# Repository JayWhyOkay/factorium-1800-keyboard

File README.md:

# Factorium Keyboard

Factorium is a keyboard in CP layout inspired by CFTKB's Discipline and Mysterium Keyboard

**Project is in hiatus indefinitely until further notice **

## Differences between Mysterium and Factorium
- Added numpad 
- Move arrow keys down and right
- Addition of F13
- Removal of two navigation buttons 

## ToDo
- Standardize placement of arrows and num cluster to proper unit ratios (0.25 down and right for arrow keys, 1.25U for numpad)
- Adjust mounting points to be equidistant from the edges 
- Create smaller logo for silk screen printing 
- Design Acrylic feet 

## Images
coming once prototypes are ordered

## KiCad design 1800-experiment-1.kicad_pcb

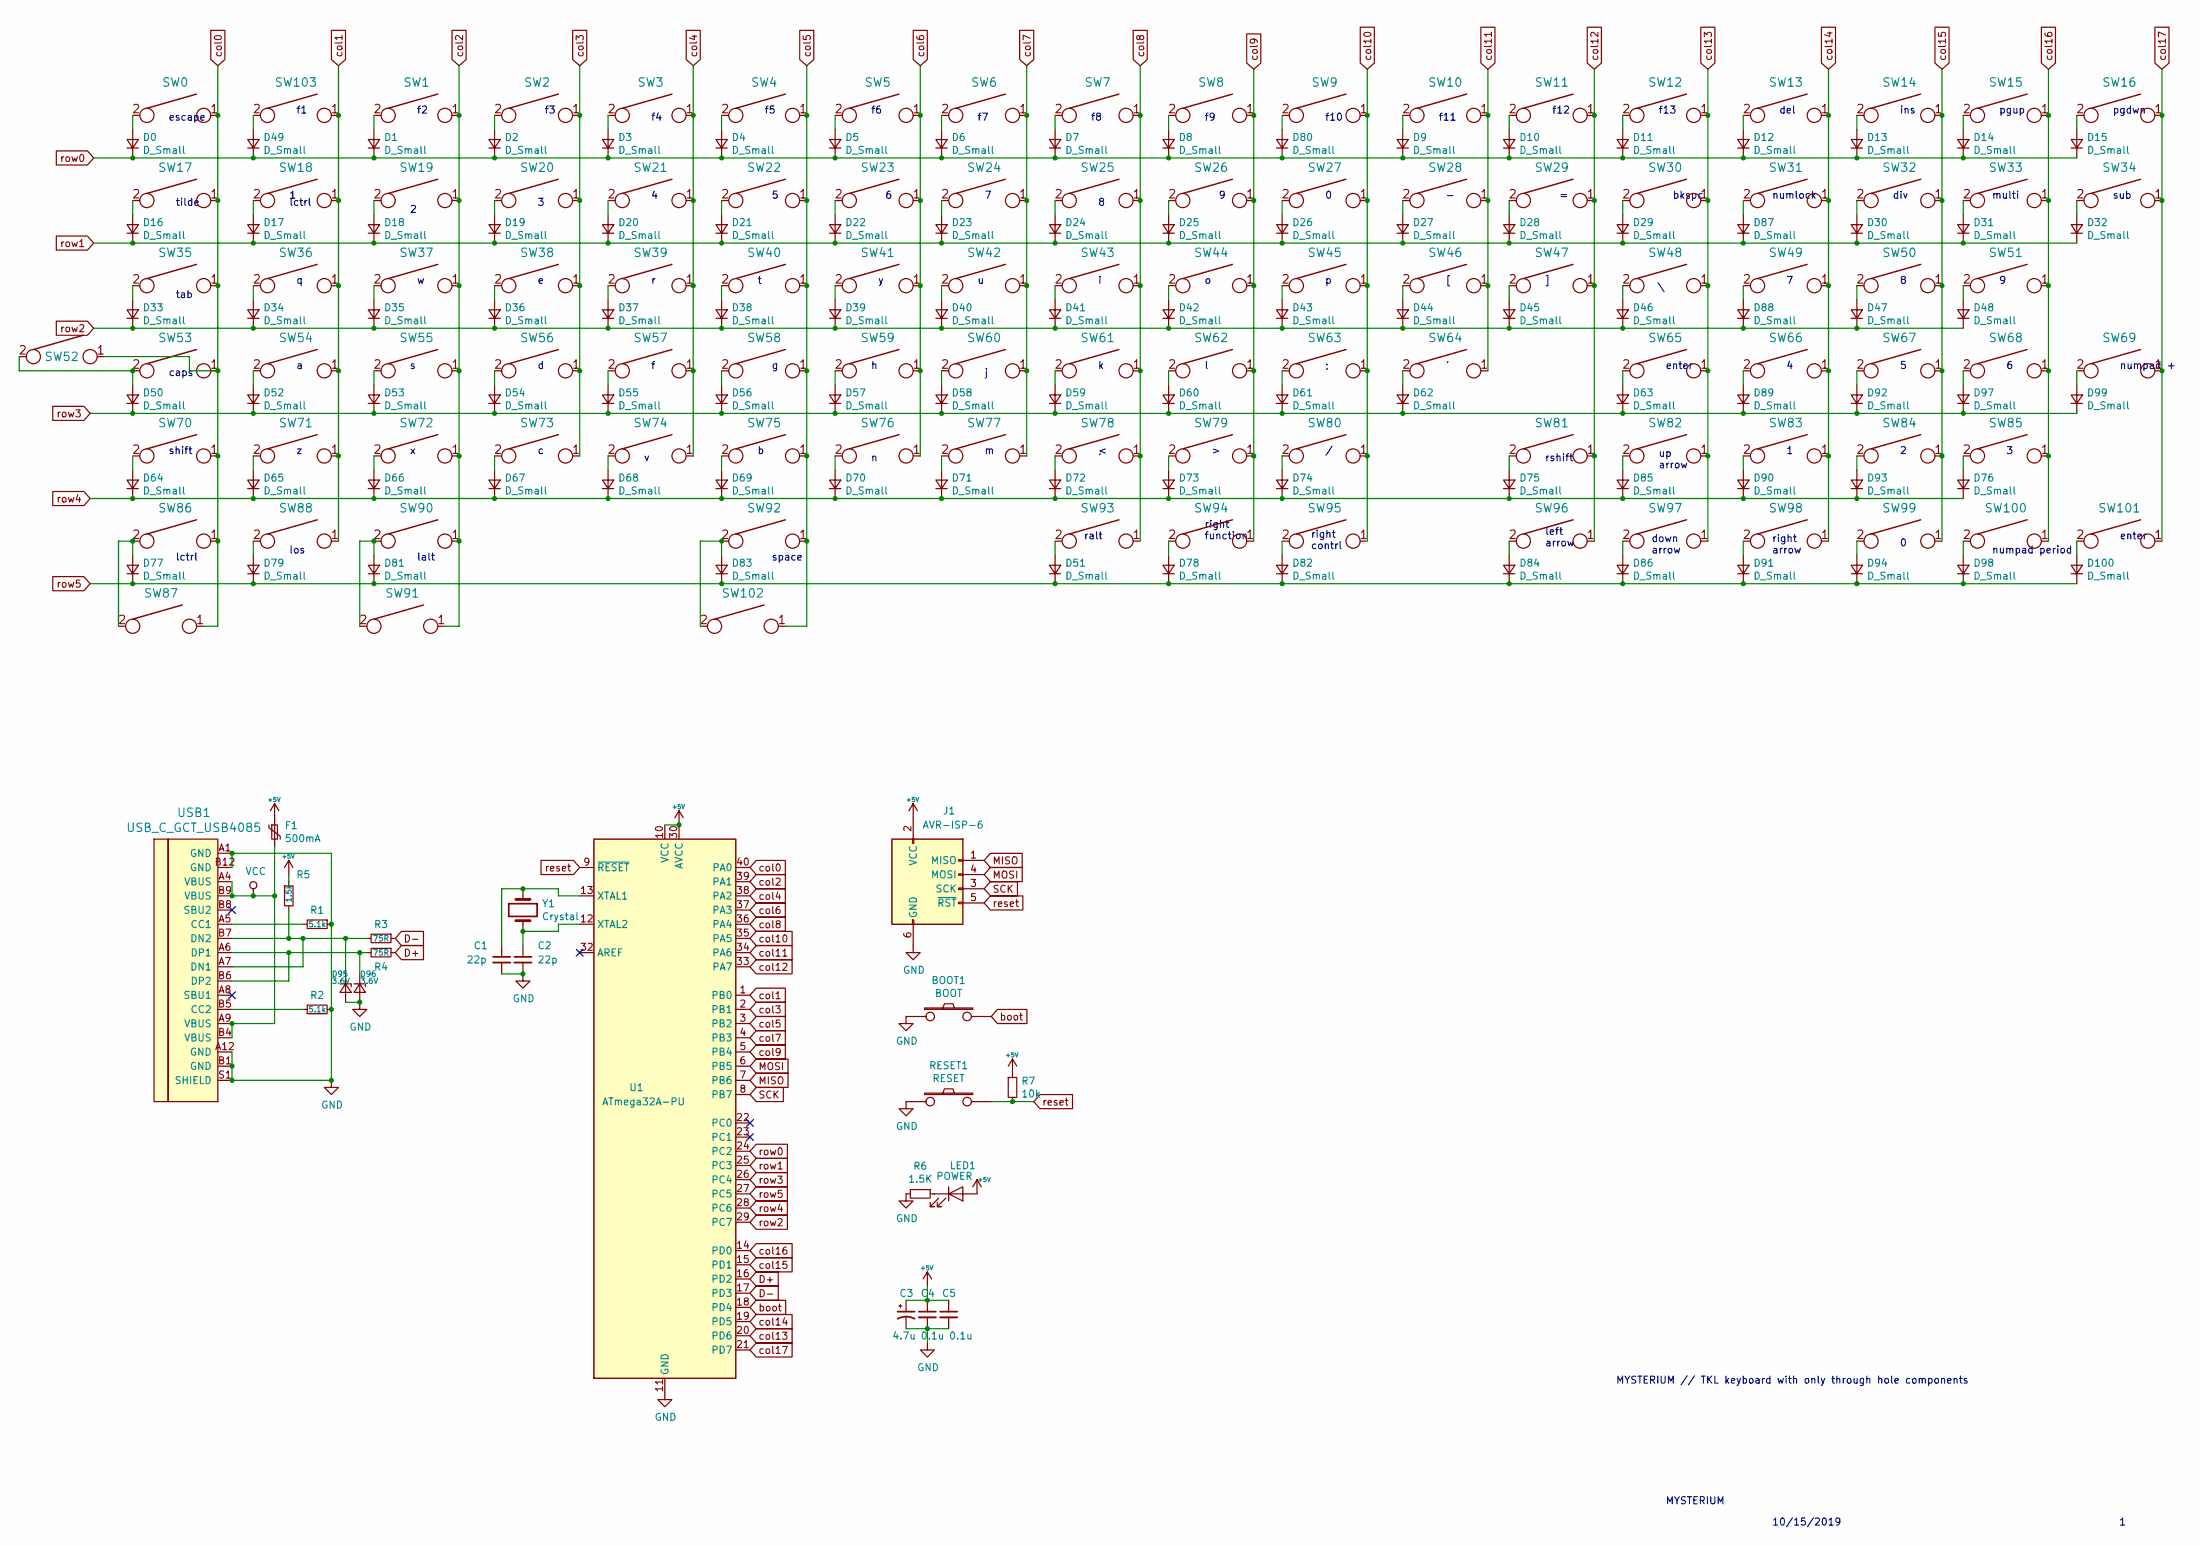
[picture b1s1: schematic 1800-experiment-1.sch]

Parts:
BOOT1: BOOT; SW_PUSH_6mm
C1, C2: 22p; C_Disc_D3.0mm_W1.6mm_P2.50mm
C3: 4.7u; CP_Radial_D4.0mm_P1.50mm
C4, C5: 0.1u; C_Disc_D4.3mm_W1.9mm_P5.00mm
D0, D1, D2, D3, D4, D5, D6, D7, D8, D9, D10, D11, D12, D13, D14, D15, D16, D17, D18, D19, D20, D21, D22, D23, D24, D25, D26, D27, D28, D29, D30, D31, D32, D33, D34, D35, D36, D37, D38, D39, D40, D41, D42, D43, D44, D45, D46, D47, D48, D49, D50, D51, D52, D53, D54, D55, D56, D57, D58, D59, D60, D61, D62, D63, D64, D65, D66, D67, D68, D69, D70, D71, D72, D73, D74, D75, D76, D77, D78, D79, D80, D81, D82, D83, D84, D85, D86, D87, D88, D89, D90, D91, D92, D93, D94, D97, D98, D99, D100: D_Small; D_DO-35_SOD27_P5.08mm_Horizontal
D95, D96: 3.6V; D_DO-35_SOD27_P5.08mm_Horizontal
F1: 500mA; polyfuse_5.1mm
J1: AVR-ISP-6; AVR_ICSP_3x2
LED1: POWER; LED_D3.0mm
R1, R2: 5.1k; R_Axial_DIN0204_L3.6mm_D1.6mm_P7.62mm_Horizontal
R3, R4: 75R; R_Axial_DIN0204_L3.6mm_D1.6mm_P7.62mm_Horizontal
R5: 1.5k; R_Axial_DIN0204_L3.6mm_D1.6mm_P7.62mm_Horizontal
R6: 1.5K; R_Axial_DIN0204_L3.6mm_D1.6mm_P7.62mm_Horizontal
R7: 10k; R_Axial_DIN0204_L3.6mm_D1.6mm_P7.62mm_Horizontal
RESET1: RESET; SW_PUSH_6mm
SW0, SW1, SW2, SW3, SW4, SW5, SW6, SW7, SW8, SW10, SW11, SW12, SW13, SW14, SW15, SW16, SW17, SW18, SW19, SW20, SW21, SW22, SW23, SW24, SW25, SW26, SW27, SW28, SW29, SW30, SW31, SW32, SW33, SW34, SW36, SW37, SW38, SW39, SW40, SW41, SW42, SW43, SW44, SW45, SW46, SW47, SW49, SW50, SW51, SW54, SW55, SW56, SW57, SW58, SW59, SW60, SW61, SW62, SW63, SW64, SW66, SW67, SW68, SW71, SW72, SW73, SW74, SW75, SW76, SW77, SW78, SW79, SW80, SW82, SW83, SW84, SW85, SW92, SW96, SW97, SW98, SW99, SW100, SW102, SW103: KEYSW; SW_Cherry_MX1A_1.00u_PCB-NOSCREEN
SW9, SW52, SW87, SW88, SW91, SW93, SW94, SW95: KEYSW; SW_Cherry_MX1A_1.25u_PCBNOSCREEN
SW35, SW48, SW86, SW90: KEYSW; SW_Cherry_MX1A_1.50u_PCBNOSCREEN
SW53, SW81: KEYSW; SW_Cherry_MX1A_1.75u_PCBNOSCREEN
SW65, SW70: KEYSW; SW_Cherry_MX1A_2.25u_PCBNOSCREEN
SW69, SW101: KEYSW; SW_Cherry_MX1A_2.00u_PCBNOSCREEN
U1: ATmega32A-PU; DIP-40_W15.24mm
USB1: USB_C_GCT_USB4085
Y1: Crystal; Crystal_HC49-4H_Vertical

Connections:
+5V: C3.1, C4.1, C5.1, F1.1, J1.2 (VCC), LED1.2 (A), R5.1, R7.1, U1.10 (VCC), U1.30 (AVCC)
D+: R4.1, U1.16 (PD2)
D-: R3.1, U1.17 (PD3)
GND: BOOT1.1, C1.2, C2.2, C3.2, C4.2, C5.2, D95.2 (A), D96.2 (A), J1.6 (GND), R1.1, R2.2, R6.2, RESET1.1, U1.11 (GND), U1.31 (GND), USB1.A1 (GND), USB1.A12 (GND), USB1.B1 (GND), USB1.B12 (GND), USB1.S1 (SHIELD)
MISO: J1.1 (MISO), U1.7 (PB6)
MOSI: J1.4 (MOSI), U1.6 (PB5)
unnamed: C1.1, U1.13 (XTAL1), Y1.1
unnamed: C2.1, U1.12 (XTAL2), Y1.2
unnamed: D0.2 (A), SW0.2
unnamed: D1.2 (A), SW1.2
unnamed: D2.2 (A), SW2.2
unnamed: D3.2 (A), SW3.2
unnamed: D4.2 (A), SW4.2
unnamed: D5.2 (A), SW5.2
unnamed: D6.2 (A), SW6.2
unnamed: D7.2 (A), SW7.2
unnamed: D8.2 (A), SW8.2
unnamed: D9.2 (A), SW10.2
unnamed: D10.2 (A), SW11.2
unnamed: D11.2 (A), SW12.2
unnamed: D12.2 (A), SW13.2
unnamed: D13.2 (A), SW14.2
unnamed: D14.2 (A), SW15.2
unnamed: D15.2 (A), SW16.2
unnamed: D16.2 (A), SW17.2
unnamed: D17.2 (A), SW18.2
unnamed: D18.2 (A), SW19.2
unnamed: D19.2 (A), SW20.2
unnamed: D20.2 (A), SW21.2
unnamed: D21.2 (A), SW22.2
unnamed: D22.2 (A), SW23.2
unnamed: D23.2 (A), SW24.2
unnamed: D24.2 (A), SW25.2
unnamed: D25.2 (A), SW26.2
unnamed: D26.2 (A), SW27.2
unnamed: D27.2 (A), SW28.2
unnamed: D28.2 (A), SW29.2
unnamed: D29.2 (A), SW30.2
unnamed: D30.2 (A), SW32.2
unnamed: D31.2 (A), SW33.2
unnamed: D32.2 (A), SW34.2
unnamed: D33.2 (A), SW35.2
unnamed: D34.2 (A), SW36.2
unnamed: D35.2 (A), SW37.2
unnamed: D36.2 (A), SW38.2
unnamed: D37.2 (A), SW39.2
unnamed: D38.2 (A), SW40.2
unnamed: D39.2 (A), SW41.2
unnamed: D40.2 (A), SW42.2
unnamed: D41.2 (A), SW43.2
unnamed: D42.2 (A), SW44.2
unnamed: D43.2 (A), SW45.2
unnamed: D44.2 (A), SW46.2
unnamed: D45.2 (A), SW47.2
unnamed: D46.2 (A), SW48.2
unnamed: D47.2 (A), SW50.2
unnamed: D48.2 (A), SW51.2
unnamed: D49.2 (A), SW103.2
unnamed: D50.2 (A), SW52.2, SW53.2
unnamed: D51.2 (A), SW93.2
unnamed: D52.2 (A), SW54.2
unnamed: D53.2 (A), SW55.2
unnamed: D54.2 (A), SW56.2
unnamed: D55.2 (A), SW57.2
unnamed: D56.2 (A), SW58.2
unnamed: D57.2 (A), SW59.2
unnamed: D58.2 (A), SW60.2
unnamed: D59.2 (A), SW61.2
unnamed: D60.2 (A), SW62.2
unnamed: D61.2 (A), SW63.2
unnamed: D62.2 (A), SW64.2
unnamed: D63.2 (A), SW65.2
unnamed: D64.2 (A), SW70.2
unnamed: D65.2 (A), SW71.2
unnamed: D66.2 (A), SW72.2
unnamed: D67.2 (A), SW73.2
unnamed: D68.2 (A), SW74.2
unnamed: D69.2 (A), SW75.2
unnamed: D70.2 (A), SW76.2
unnamed: D71.2 (A), SW77.2
unnamed: D72.2 (A), SW78.2
unnamed: D73.2 (A), SW79.2
unnamed: D74.2 (A), SW80.2
unnamed: D75.2 (A), SW81.2
unnamed: D76.2 (A), SW85.2
unnamed: D77.2 (A), SW86.2, SW87.2
unnamed: D78.2 (A), SW94.2
unnamed: D79.2 (A), SW88.2
unnamed: D80.2 (A), SW9.2
unnamed: D81.2 (A), SW90.2, SW91.2
unnamed: D82.2 (A), SW95.2
unnamed: D83.2 (A), SW92.2, SW102.2
unnamed: D84.2 (A), SW96.2
unnamed: D85.2 (A), SW82.2
unnamed: D86.2 (A), SW97.2
unnamed: D87.2 (A), SW31.2
unnamed: D88.2 (A), SW49.2
unnamed: D89.2 (A), SW66.2
unnamed: D90.2 (A), SW83.2
unnamed: D91.2 (A), SW98.2
unnamed: D92.2 (A), SW67.2
unnamed: D93.2 (A), SW84.2
unnamed: D94.2 (A), SW99.2
unnamed: D95.1 (K), R3.2, R5.2, USB1.A7 (DN1), USB1.B7 (DN2)
unnamed: D96.1 (K), R4.2, USB1.A6 (DP1), USB1.B6 (DP2)
unnamed: D97.2 (A), SW68.2
unnamed: D98.2 (A), SW100.2
unnamed: D99.2 (A), SW69.2
unnamed: D100.2 (A), SW101.2
unnamed: LED1.1 (K), R6.1
unnamed: R1.2, USB1.A5 (CC1)
unnamed: R2.1, USB1.B5 (CC2)
SCK: J1.3 (SCK), U1.8 (PB7)
VCC: F1.2, USB1.A4 (VBUS), USB1.A9 (VBUS), USB1.B4 (VBUS), USB1.B9 (VBUS)
boot: BOOT1.2, U1.18 (PD4)
col0: SW0.1, SW17.1, SW35.1, SW52.1, SW53.1, SW70.1, SW86.1, SW87.1, U1.40 (PA0)
col1: SW18.1, SW36.1, SW54.1, SW71.1, SW88.1, SW103.1, U1.1 (PB0)
col2: SW1.1, SW19.1, SW37.1, SW55.1, SW72.1, SW90.1, SW91.1, U1.39 (PA1)
col3: SW2.1, SW20.1, SW38.1, SW56.1, SW73.1, U1.2 (PB1)
col4: SW3.1, SW21.1, SW39.1, SW57.1, SW74.1, U1.38 (PA2)
col5: SW4.1, SW22.1, SW40.1, SW58.1, SW75.1, SW92.1, SW102.1, U1.3 (PB2)
col6: SW5.1, SW23.1, SW41.1, SW59.1, SW76.1, U1.37 (PA3)
col7: SW6.1, SW24.1, SW42.1, SW60.1, SW77.1, U1.4 (PB3)
col8: SW7.1, SW25.1, SW43.1, SW61.1, SW78.1, SW93.1, U1.36 (PA4)
col9: SW8.1, SW26.1, SW44.1, SW62.1, SW79.1, SW94.1, U1.5 (PB4)
col10: SW9.1, SW27.1, SW45.1, SW63.1, SW80.1, SW95.1, U1.35 (PA5)
col11: SW10.1, SW28.1, SW46.1, SW64.1, U1.34 (PA6)
col12: SW11.1, SW29.1, SW47.1, SW81.1, SW96.1, U1.33 (PA7)
col13: SW12.1, SW30.1, SW48.1, SW65.1, SW82.1, SW97.1, U1.20 (PD6)
col14: SW13.1, SW31.1, SW49.1, SW66.1, SW83.1, SW98.1, U1.19 (PD5)
col15: SW14.1, SW32.1, SW50.1, SW67.1, SW84.1, SW99.1, U1.15 (PD1)
col16: SW15.1, SW33.1, SW51.1, SW68.1, SW85.1, SW100.1, U1.14 (PD0)
col17: SW16.1, SW34.1, SW69.1, SW101.1, U1.21 (PD7)
reset: J1.5 (~RST), R7.2, RESET1.2, U1.9 (~RESET)
row0: D0.1 (K), D1.1 (K), D2.1 (K), D3.1 (K), D4.1 (K), D5.1 (K), D6.1 (K), D7.1 (K), D8.1 (K), D9.1 (K), D10.1 (K), D11.1 (K), D12.1 (K), D13.1 (K), D14.1 (K), D15.1 (K), D49.1 (K), D80.1 (K), U1.24 (PC2)
row1: D16.1 (K), D17.1 (K), D18.1 (K), D19.1 (K), D20.1 (K), D21.1 (K), D22.1 (K), D23.1 (K), D24.1 (K), D25.1 (K), D26.1 (K), D27.1 (K), D28.1 (K), D29.1 (K), D30.1 (K), D31.1 (K), D32.1 (K), D87.1 (K), U1.25 (PC3)
row2: D33.1 (K), D34.1 (K), D35.1 (K), D36.1 (K), D37.1 (K), D38.1 (K), D39.1 (K), D40.1 (K), D41.1 (K), D42.1 (K), D43.1 (K), D44.1 (K), D45.1 (K), D46.1 (K), D47.1 (K), D48.1 (K), D88.1 (K), U1.29 (PC7)
row3: D50.1 (K), D52.1 (K), D53.1 (K), D54.1 (K), D55.1 (K), D56.1 (K), D57.1 (K), D58.1 (K), D59.1 (K), D60.1 (K), D61.1 (K), D62.1 (K), D63.1 (K), D89.1 (K), D92.1 (K), D97.1 (K), D99.1 (K), U1.26 (PC4)
row4: D64.1 (K), D65.1 (K), D66.1 (K), D67.1 (K), D68.1 (K), D69.1 (K), D70.1 (K), D71.1 (K), D72.1 (K), D73.1 (K), D74.1 (K), D75.1 (K), D76.1 (K), D85.1 (K), D90.1 (K), D93.1 (K), U1.28 (PC6)
row5: D51.1 (K), D77.1 (K), D78.1 (K), D79.1 (K), D81.1 (K), D82.1 (K), D83.1 (K), D84.1 (K), D86.1 (K), D91.1 (K), D94.1 (K), D98.1 (K), D100.1 (K), U1.27 (PC5)

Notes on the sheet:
MYSTERIUM // TKL keyboard with only through hole components
10/15/2019
MYSTERIUM
escape
tilde
tab
caps
shift
lctrl
lctrl
los
f10
f11
f12
bkspc
lalt
space
ralt
f13
del
ins
pgup
pgdwn
numlock
div
multi
sub
numpad +
enter
numpad period
enter
rshift
down arrow
up arrow
right arrow
left arrow
right function
right contrl

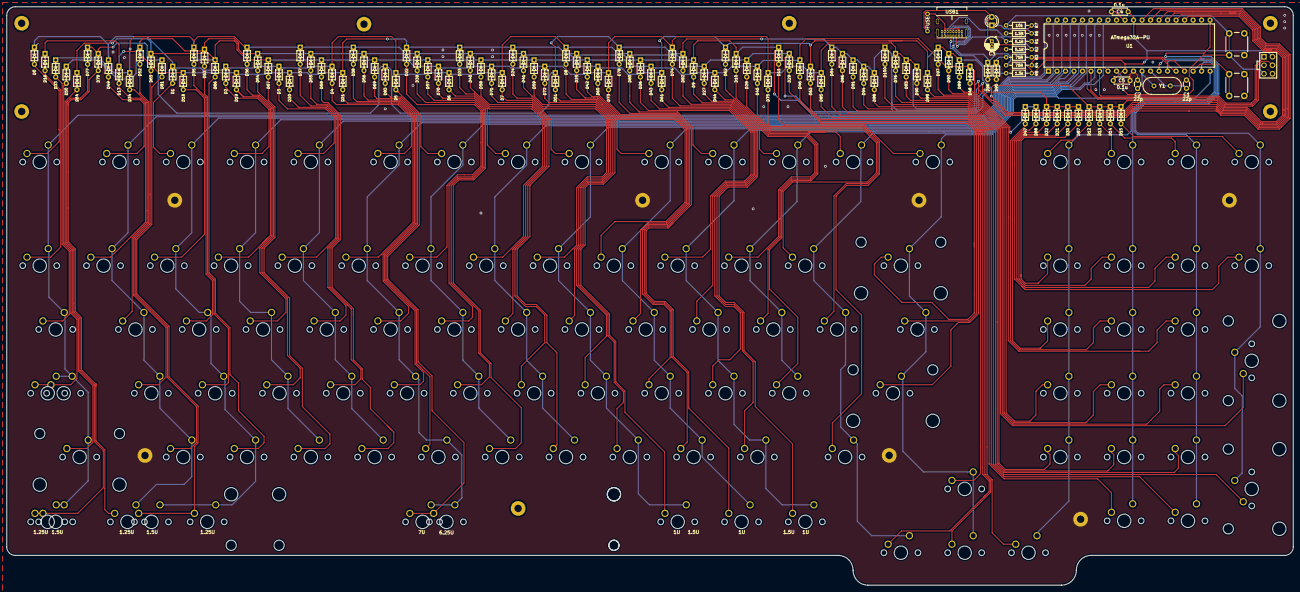
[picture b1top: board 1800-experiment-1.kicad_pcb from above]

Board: 2 copper layers, 384.2 x 172.7 mm, 225 parts (0 on the bottom side), 140 nets.

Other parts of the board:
ST72: 7U; MX-7U-Stabilizer

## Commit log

2020-06-14 Initial commit w/ edits
2020-06-23 pcb design v1
2020-06-23 added gitignore
2020-06-23 refactoring and cleaning up
2020-06-23 gitignore changes
2020-06-23 gitignore properly working
2020-06-23 Quick change to readme
2020-06-23 inserted m2 standoffs for mounting
2020-06-24 cleanup of files and m4 screws for feet
2020-06-24 work on bottom plate
2020-06-24 gerber fles for pcb generated
2020-06-24 start on plate
2020-06-24 cleanup of files
2020-07-03 addition of plate
2020-07-15 addition of acrylic guard
2020-07-15 Readme updates
